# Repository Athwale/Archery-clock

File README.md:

# REV1 boards have not been built and tested yet.
If you intend to build it, please wait.

# Archery-clock
This repository contains electronic designs and software for a custom built sport archery clock used by www.patriotbrno.cz

## V2
V2 is the current design which uses a Raspberry pi 3 and is controlled over wi-fi using a smartphone or a computer.  
It is built to be more modular and easier to build or repair.

## PCBs
The DXF and Gerber files are exported from copper side and must be mirror flipped by the manufacturer to produce correct boards, KiCad does not have this functionality built in. Drill files are included, but should be checked and adjusted according to your needs.  
Check the position of pin 1 on the microcontroller (square pad in the design) for correct stencil placement.

## Control software  
The clock has a web based user interface that you can use from a wif-fi capable phone or computer.  
This software is being developed here:  
https://github.com/zmej/arclock

### Viewing the designs
Electronic designs were made in KiCad.

### Disclaimer
These designs were not professionally produced nor rigorously tested by any institution. You are building this device on your own and you accept all responsibility for it's function and operation.

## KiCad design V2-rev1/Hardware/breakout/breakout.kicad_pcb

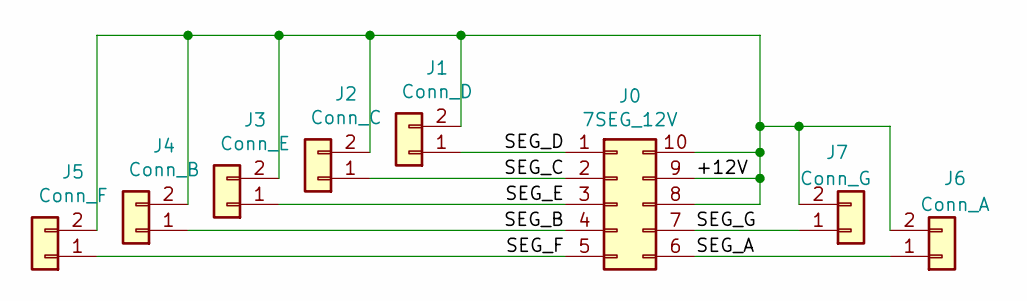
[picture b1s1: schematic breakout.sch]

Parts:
J0: 7SEG_12V; IDC-Header_2x05-1MP_P2.54mm_Latch_Vertical
J1: Conn_D; Molex_KK-254_AE-6410-02A_1x02_P2.54mm_Vertical
J2: Conn_C; Molex_KK-254_AE-6410-02A_1x02_P2.54mm_Vertical
J3: Conn_E; Molex_KK-254_AE-6410-02A_1x02_P2.54mm_Vertical
J4: Conn_B; Molex_KK-254_AE-6410-02A_1x02_P2.54mm_Vertical
J5: Conn_F; Molex_KK-254_AE-6410-02A_1x02_P2.54mm_Vertical
J6: Conn_A; Molex_KK-254_AE-6410-02A_1x02_P2.54mm_Vertical
J7: Conn_G; Molex_KK-254_AE-6410-02A_1x02_P2.54mm_Vertical

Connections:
/+12V: J0.8, J0.9, J0.10, J1.2, J2.2, J3.2, J4.2, J5.2, J6.2, J7.2
/SEG_A: J0.6, J6.1
/SEG_B: J0.4, J4.1
/SEG_C: J0.2, J2.1
/SEG_D: J0.1, J1.1
/SEG_E: J0.3, J3.1
/SEG_F: J0.5, J5.1
/SEG_G: J0.7, J7.1

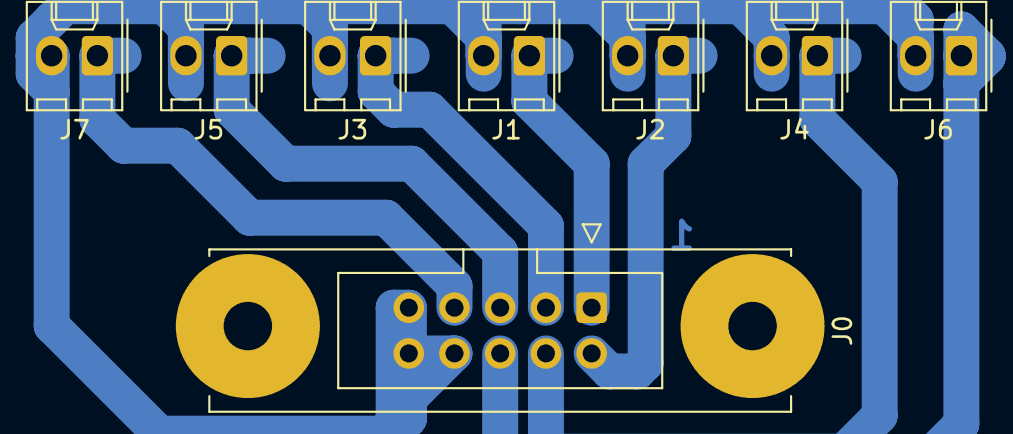
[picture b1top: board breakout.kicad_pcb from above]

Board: 2 copper layers, 12 parts (0 on the bottom side), 8 nets.

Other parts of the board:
Screw: MountingHole_3.2mm_M3
Screw#2, Screw#3, Screw#4: MountingHole_3.2mm_M3

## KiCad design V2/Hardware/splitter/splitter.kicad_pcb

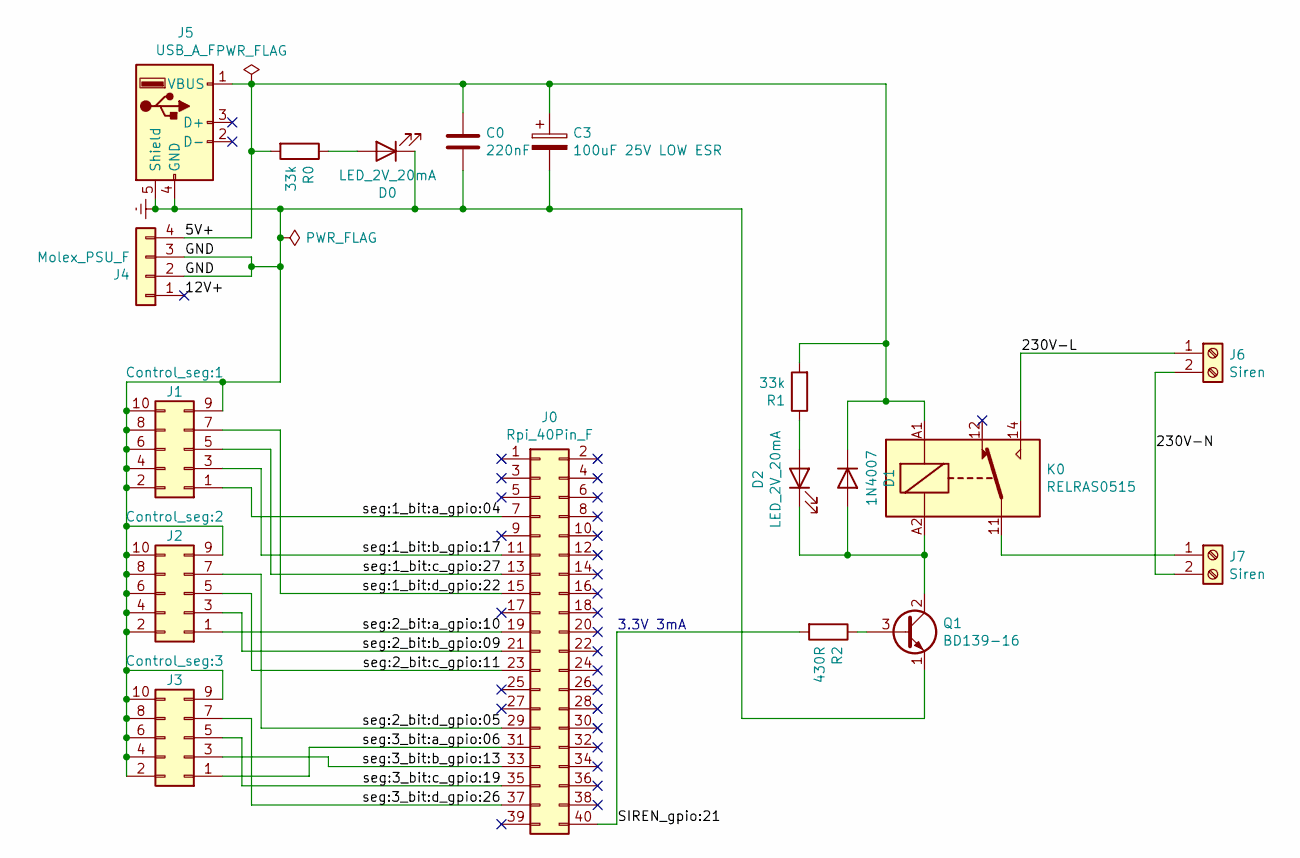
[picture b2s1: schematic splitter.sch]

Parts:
C0: 220nF; C_Disc_D4.3mm_W1.9mm_P5.00mm
C3: 100uF 25V LOW ESR; CP_Radial_D10.0mm_P5.00mm
D0, D2: LED_2V_20mA; LED_D5.0mm
D1: 1N4007; D_A-405_P10.16mm_Horizontal
J0: Rpi_40Pin_F; PinSocket_2x20_P2.54mm_Vertical
J1: Control_seg:1; IDC-Header_2x05-1MP_P2.54mm_Latch_Vertical
J2: Control_seg:2; IDC-Header_2x05-1MP_P2.54mm_Latch_Vertical
J3: Control_seg:3; IDC-Header_2x05-1MP_P2.54mm_Latch_Vertical
J4: Molex_PSU_F; conn_hdd_15-24-4449
J5: USB_A_F; USB_A_Stewart_SS-52100-001_Horizontal
J6, J7: Siren; TerminalBlock_RND_205-00067_1x02_P7.50mm_Horizontal
K0: RELRAS0515; Relay_SPDT_Finder_36.11
Q1: BD139-16; TO-126-3_Vertical
R0, R1: 33k; R_Axial_DIN0207_L6.3mm_D2.5mm_P10.16mm_Horizontal
R2: 430R; R_Axial_DIN0207_L6.3mm_D2.5mm_P10.16mm_Horizontal

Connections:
/5V+: C0.1, C3.1, D1.1 (K), J4.4, J5.1 (VBUS), K0.A1, R0.2, R1.2
/12V+: J4.1
/230V-L: J6.1, K0.14
/230V-N: J6.2, J7.2
/SIREN_gpio:21: J0.40, R2.2
/seg:1_bit:a_gpio:04: J0.7, J1.1
/seg:1_bit:b_gpio:17: J0.11, J1.3
/seg:1_bit:c_gpio:27: J0.13, J1.5
/seg:1_bit:d_gpio:22: J0.15, J1.7
/seg:2_bit:a_gpio:10: J0.19, J2.1
/seg:2_bit:b_gpio:09: J0.21, J2.3
/seg:2_bit:c_gpio:11: J0.23, J2.5
/seg:2_bit:d_gpio:05: J0.29, J2.7
/seg:3_bit:a_gpio:06: J0.31, J3.1
/seg:3_bit:b_gpio:13: J0.33, J3.3
/seg:3_bit:c_gpio:19: J0.35, J3.5
/seg:3_bit:d_gpio:26: J0.37, J3.7
Earth: C0.2, C3.2, D0.1 (K), J1.2, J1.4, J1.6, J1.8, J1.9, J1.10, J2.2, J2.4, J2.6, J2.8, J2.9, J2.10, J3.2, J3.4, J3.6, J3.8, J3.9, J3.10, J4.2, J4.3, J5.4 (GND), J5.5 (Shield), Q1.1 (E)
unnamed: D0.2 (A), R0.1
unnamed: D1.2 (A), D2.1 (K), K0.A2, Q1.2 (C)
unnamed: D2.2 (A), R1.1
unnamed: J7.1, K0.11
unnamed: Q1.3 (B), R2.1

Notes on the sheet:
3.3V 3mA

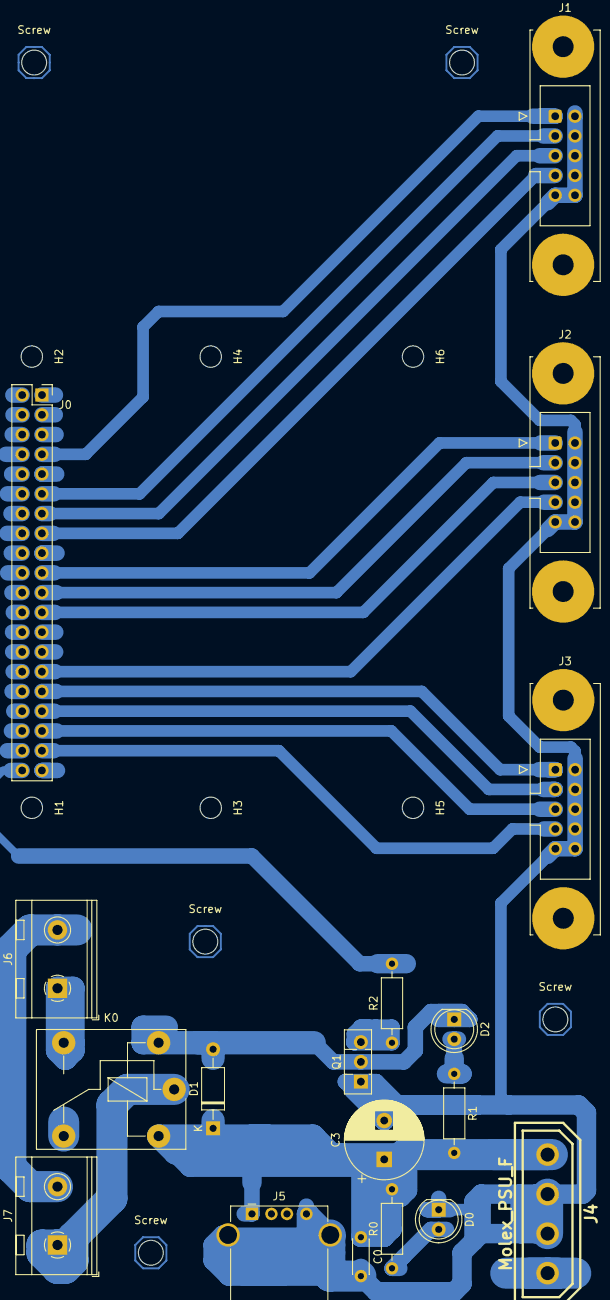
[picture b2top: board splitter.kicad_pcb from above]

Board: 2 copper layers, 29 parts (0 on the bottom side), 22 nets.

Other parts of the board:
H1, H2, H3, H4, H5, H6: MountingHole; MountingHole_2.75mm_NoPad
Screw: MountingHole_3.2mm_M3
Screw#2, Screw#3, Screw#4, Screw#5: MountingHole_3.2mm_M3

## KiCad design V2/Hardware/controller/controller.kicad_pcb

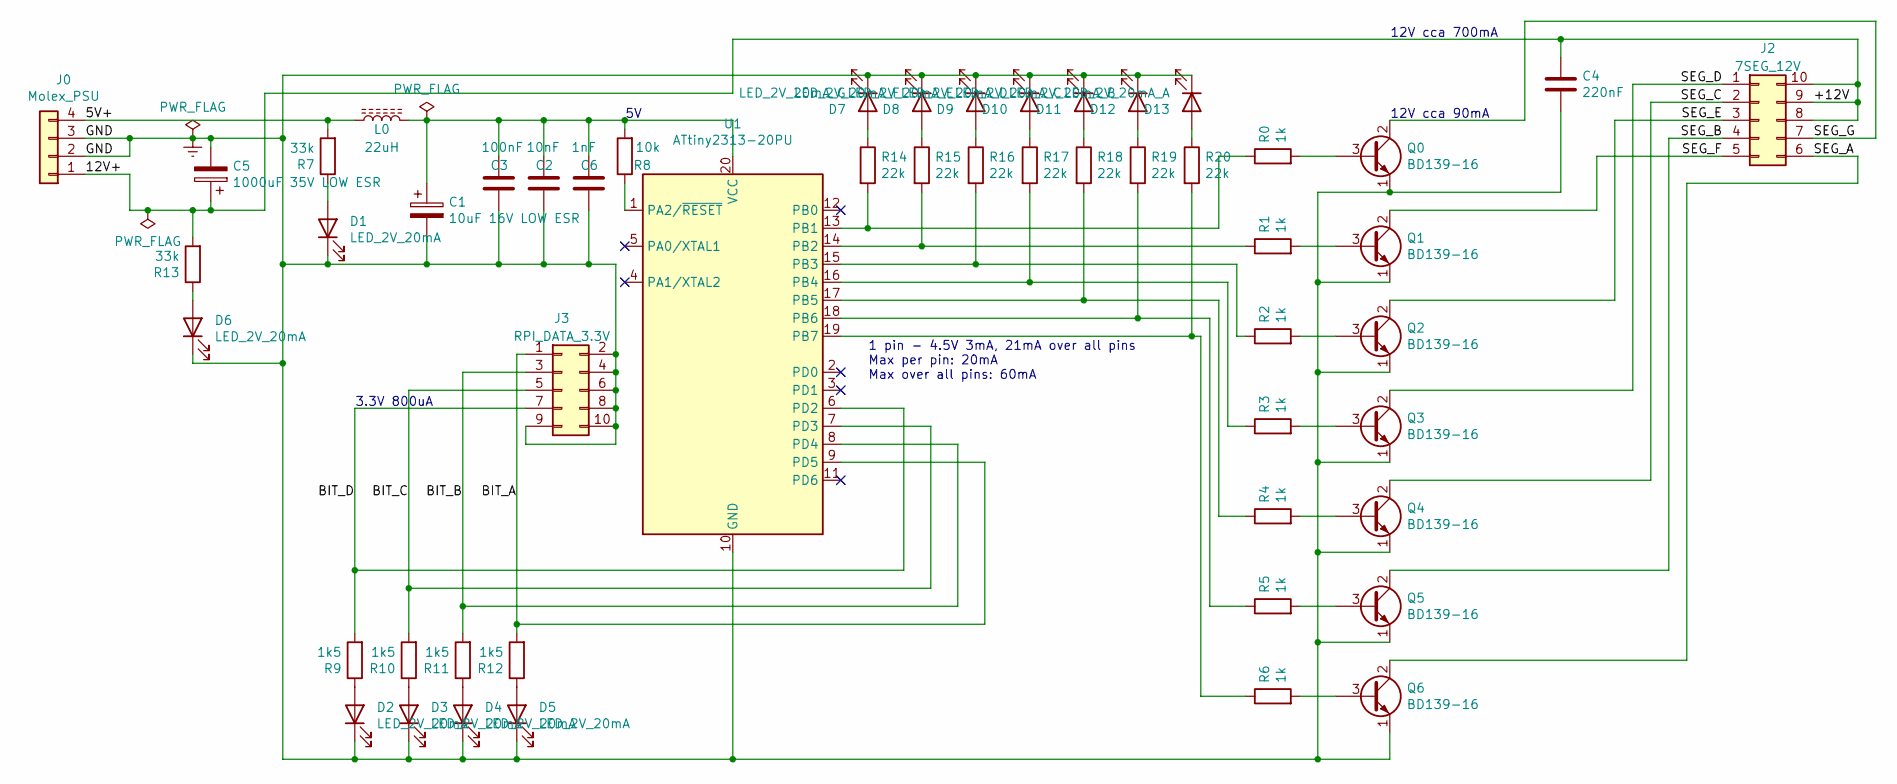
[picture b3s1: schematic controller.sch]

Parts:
C1: 10uF 16V LOW ESR; CP_Radial_D5.0mm_P2.00mm
C2: 10nF; C_Disc_D5.0mm_W2.5mm_P5.00mm
C3: 100nF; C_Disc_D5.0mm_W2.5mm_P5.00mm
C4: 220nF; C_Disc_D5.0mm_W2.5mm_P5.00mm
C5: 1000uF 35V LOW ESR; CP_Radial_D12.5mm_P5.00mm
C6: 1nF; C_Disc_D5.0mm_W2.5mm_P5.00mm
D1, D2, D3, D4, D5, D6: LED_2V_20mA; LED_D5.0mm
D7: LED_2V_20mA_G; LED_D5.0mm
D8: LED_2V_20mA_F; LED_D5.0mm
D9: LED_2V_20mA_E; LED_D5.0mm
D10: LED_2V_20mA_D; LED_D5.0mm
D11: LED_2V_20mA_C; LED_D5.0mm
D12: LED_2V_20mA_B; LED_D5.0mm
D13: LED_2V_20mA_A; LED_D5.0mm
J0: Molex_PSU; conn_hdd_15-24-4449
J2: 7SEG_12V; IDC-Header_2x05-1MP_P2.54mm_Latch_Vertical
J3: RPI_DATA_3.3V; IDC-Header_2x05-1MP_P2.54mm_Latch_Vertical
L0: 22uH; L_Axial_L7.0mm_D3.3mm_P10.16mm_Horizontal_Fastron_MICC
Q0, Q1, Q2, Q3, Q4, Q5, Q6: BD139-16; TO-126-3_Vertical
R0, R1, R2, R3, R4, R5, R6: 1k; R_Axial_DIN0207_L6.3mm_D2.5mm_P10.16mm_Horizontal
R7, R13: 33k; R_Axial_DIN0207_L6.3mm_D2.5mm_P10.16mm_Horizontal
R8: 10k; R_Axial_DIN0207_L6.3mm_D2.5mm_P10.16mm_Horizontal
R9, R10, R11, R12: 1k5; R_Axial_DIN0207_L6.3mm_D2.5mm_P10.16mm_Horizontal
R14, R18, R19, R20: 22k; R_Axial_DIN0207_L6.3mm_D2.5mm_P10.16mm_Horizontal
R15, R16, R17: 22k; R_Axial_DIN0207_L6.3mm_D2.5mm_P15.24mm_Horizontal
U1: ATtiny2313-20PU; DIP-20_W7.62mm

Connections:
/5V+: J0.4, L0.1, R7.2
/+12V: C4.1, C5.1, J0.1, J2.8, J2.9, J2.10, R13.2
/BIT_A: J3.1, R12.2, U1.9 (PD5)
/BIT_B: J3.3, R11.2, U1.8 (PD4)
/BIT_C: J3.5, R10.2, U1.7 (PD3)
/BIT_D: J3.7, R9.2, U1.6 (PD2)
/SEG_A: J2.6, Q6.2 (C)
/SEG_B: J2.4, Q5.2 (C)
/SEG_C: J2.2, Q4.2 (C)
/SEG_D: J2.1, Q3.2 (C)
/SEG_E: J2.3, Q2.2 (C)
/SEG_F: J2.5, Q1.2 (C)
/SEG_G: J2.7, Q0.2 (C)
Earth: C1.2, C2.2, C3.2, C4.2, C5.2, C6.2, D1.1 (K), D2.1 (K), D3.1 (K), D4.1 (K), D5.1 (K), D6.1 (K), D7.1 (K), D8.1 (K), D9.1 (K), D10.1 (K), D11.1 (K), D12.1 (K), D13.1 (K), J0.2, J0.3, J3.2, J3.4, J3.6, J3.8, J3.9, J3.10, Q0.1 (E), Q1.1 (E), Q2.1 (E), Q3.1 (E), Q4.1 (E), Q5.1 (E), Q6.1 (E), U1.10 (GND)
unnamed: C1.1, C2.1, C3.1, C6.1, L0.2, R8.2, U1.20 (VCC)
unnamed: D1.2 (A), R7.1
unnamed: D2.2 (A), R9.1
unnamed: D3.2 (A), R10.1
unnamed: D4.2 (A), R11.1
unnamed: D5.2 (A), R12.1
unnamed: D6.2 (A), R13.1
unnamed: D7.2 (A), R14.1
unnamed: D8.2 (A), R15.1
unnamed: D9.2 (A), R16.1
unnamed: D10.2 (A), R17.1
unnamed: D11.2 (A), R18.1
unnamed: D12.2 (A), R19.1
unnamed: D13.2 (A), R20.1
unnamed: Q0.3 (B), R0.2
unnamed: Q1.3 (B), R1.2
unnamed: Q2.3 (B), R2.2
unnamed: Q3.3 (B), R3.2
unnamed: Q4.3 (B), R4.2
unnamed: Q5.3 (B), R5.2
unnamed: Q6.3 (B), R6.2
unnamed: R0.1, R14.2, U1.13 (PB1)
unnamed: R1.1, R15.2, U1.14 (PB2)
unnamed: R8.1, U1.1 (PA2/~RESET)
unnamed: R2.1, R16.2, U1.15 (PB3)
unnamed: R3.1, R17.2, U1.16 (PB4)
unnamed: R4.1, R18.2, U1.17 (PB5)
unnamed: R5.1, R19.2, U1.18 (PB6)
unnamed: R6.1, R20.2, U1.19 (PB7)

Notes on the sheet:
12V cca 90mA
12V cca 700mA
1 pin - 4.5V 3mA, 21mA over all pins Max per pin: 20mA Max over all pins: 60mA
3.3V 800uA

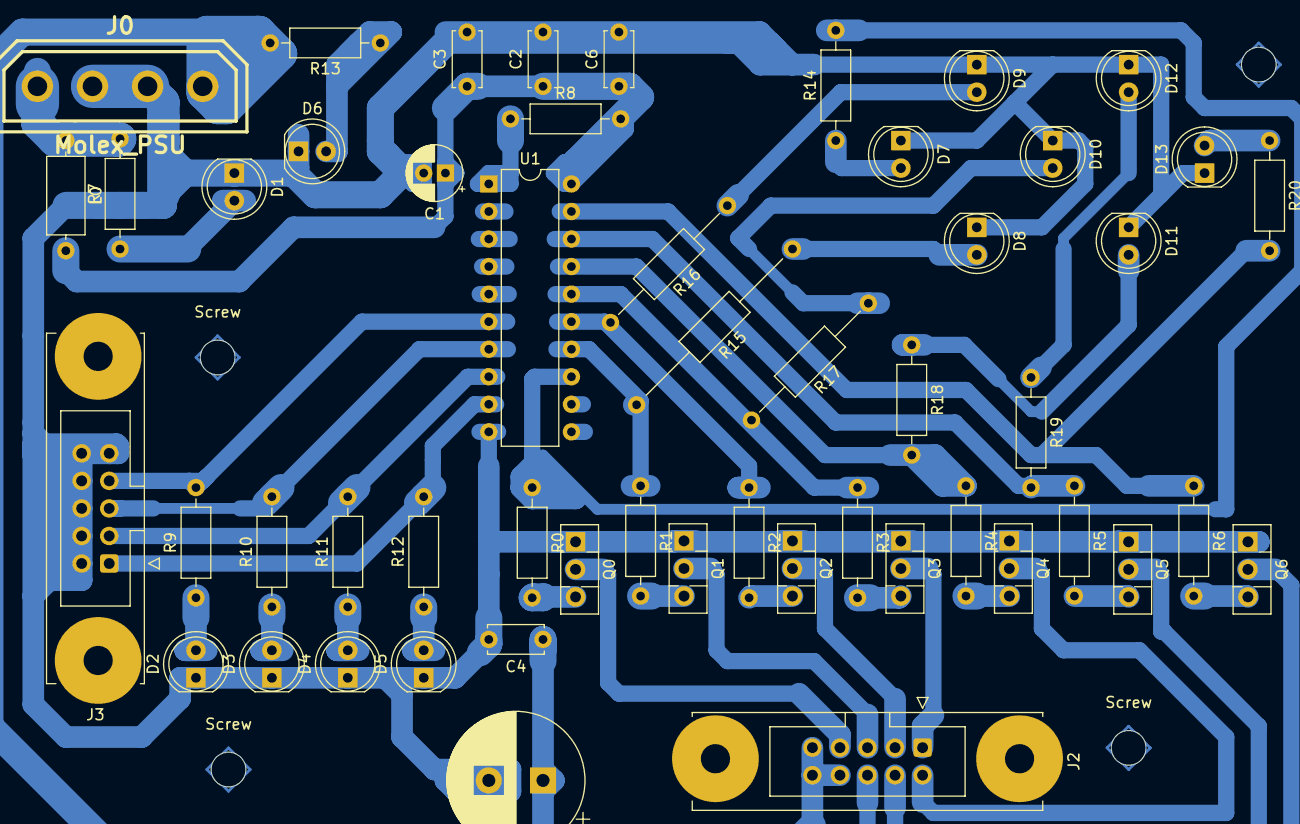
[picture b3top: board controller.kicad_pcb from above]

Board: 2 copper layers, 56 parts (0 on the bottom side), 43 nets.

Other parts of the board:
Screw: MountingHole_3.2mm_M3
Screw#2, Screw#3, Screw#4: MountingHole_3.2mm_M3

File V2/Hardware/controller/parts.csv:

"Id";"Designator";"Package";"Quantity";"Designation";"Supplier and ref";
1;"C5";"CP_Radial_D13.0mm_P5.00mm";1;"1000uF 35V LOW ESR";;;
2;"C4";"C_Disc_D5.0mm_W2.5mm_P5.00mm";1;"220nF";;;
3;"C3";"C_Disc_D5.0mm_W2.5mm_P5.00mm";1;"100nF";;;
4;"C1";"CP_Radial_D10.0mm_P5.00mm";1;"47uF";;;
5;"C2";"C_Disc_D5.0mm_W2.5mm_P5.00mm";1;"10nF";;;
6;"J2";"PinHeader_2x05_P2.54mm_Horizontal";1;"Flat_7seg_F";;;
7;"R14,R18,R19,R20";"R_Axial_DIN0207_L6.3mm_D2.5mm_P10.16mm_Horizontal";4;"22k";;;
8;"R15,R16,R17";"R_Axial_DIN0207_L6.3mm_D2.5mm_P15.24mm_Horizontal";3;"22k";;;
9;"U1";"DIP-20_W7.62mm";1;"ATtiny2313-20PU";;;
10;"D1,D2,D3,D4,D5,D6";"LED_D5.0mm";6;"LED_2V_20mA";;;
11;"D7";"LED_D5.0mm";1;"LED_2V_20mA_G";;;
12;"D8";"LED_D5.0mm";1;"LED_2V_20mA_F";;;
13;"D9";"LED_D5.0mm";1;"LED_2V_20mA_E";;;
14;"D10";"LED_D5.0mm";1;"LED_2V_20mA_D";;;
15;"D11";"LED_D5.0mm";1;"LED_2V_20mA_C";;;
16;"D12";"LED_D5.0mm";1;"LED_2V_20mA_B";;;
17;"D13";"LED_D5.0mm";1;"LED_2V_20mA_A";;;
18;"J0";"conn_hdd_15-24-4441";1;"Molex_PSU_F";;;
19;"J3";"PinHeader_2x03_P2.54mm_Horizontal";1;"Rpi_DATA_F_3.3V";;;
20;"Q0,Q1,Q2,Q3,Q4,Q5,Q6";"TO-126-3_Vertical";7;"BD139-16";;;
21;"R0,R1,R2,R3,R4,R5,R6";"R_Axial_DIN0207_L6.3mm_D2.5mm_P10.16mm_Horizontal";7;"1k";;;
22;"R7,R13";"R_Axial_DIN0207_L6.3mm_D2.5mm_P10.16mm_Horizontal";2;"33k";;;
23;"R8";"R_Axial_DIN0207_L6.3mm_D2.5mm_P10.16mm_Horizontal";1;"10k";;;
24;"R9,R10,R11,R12";"R_Axial_DIN0207_L6.3mm_D2.5mm_P10.16mm_Horizontal";4;"1k5";;;

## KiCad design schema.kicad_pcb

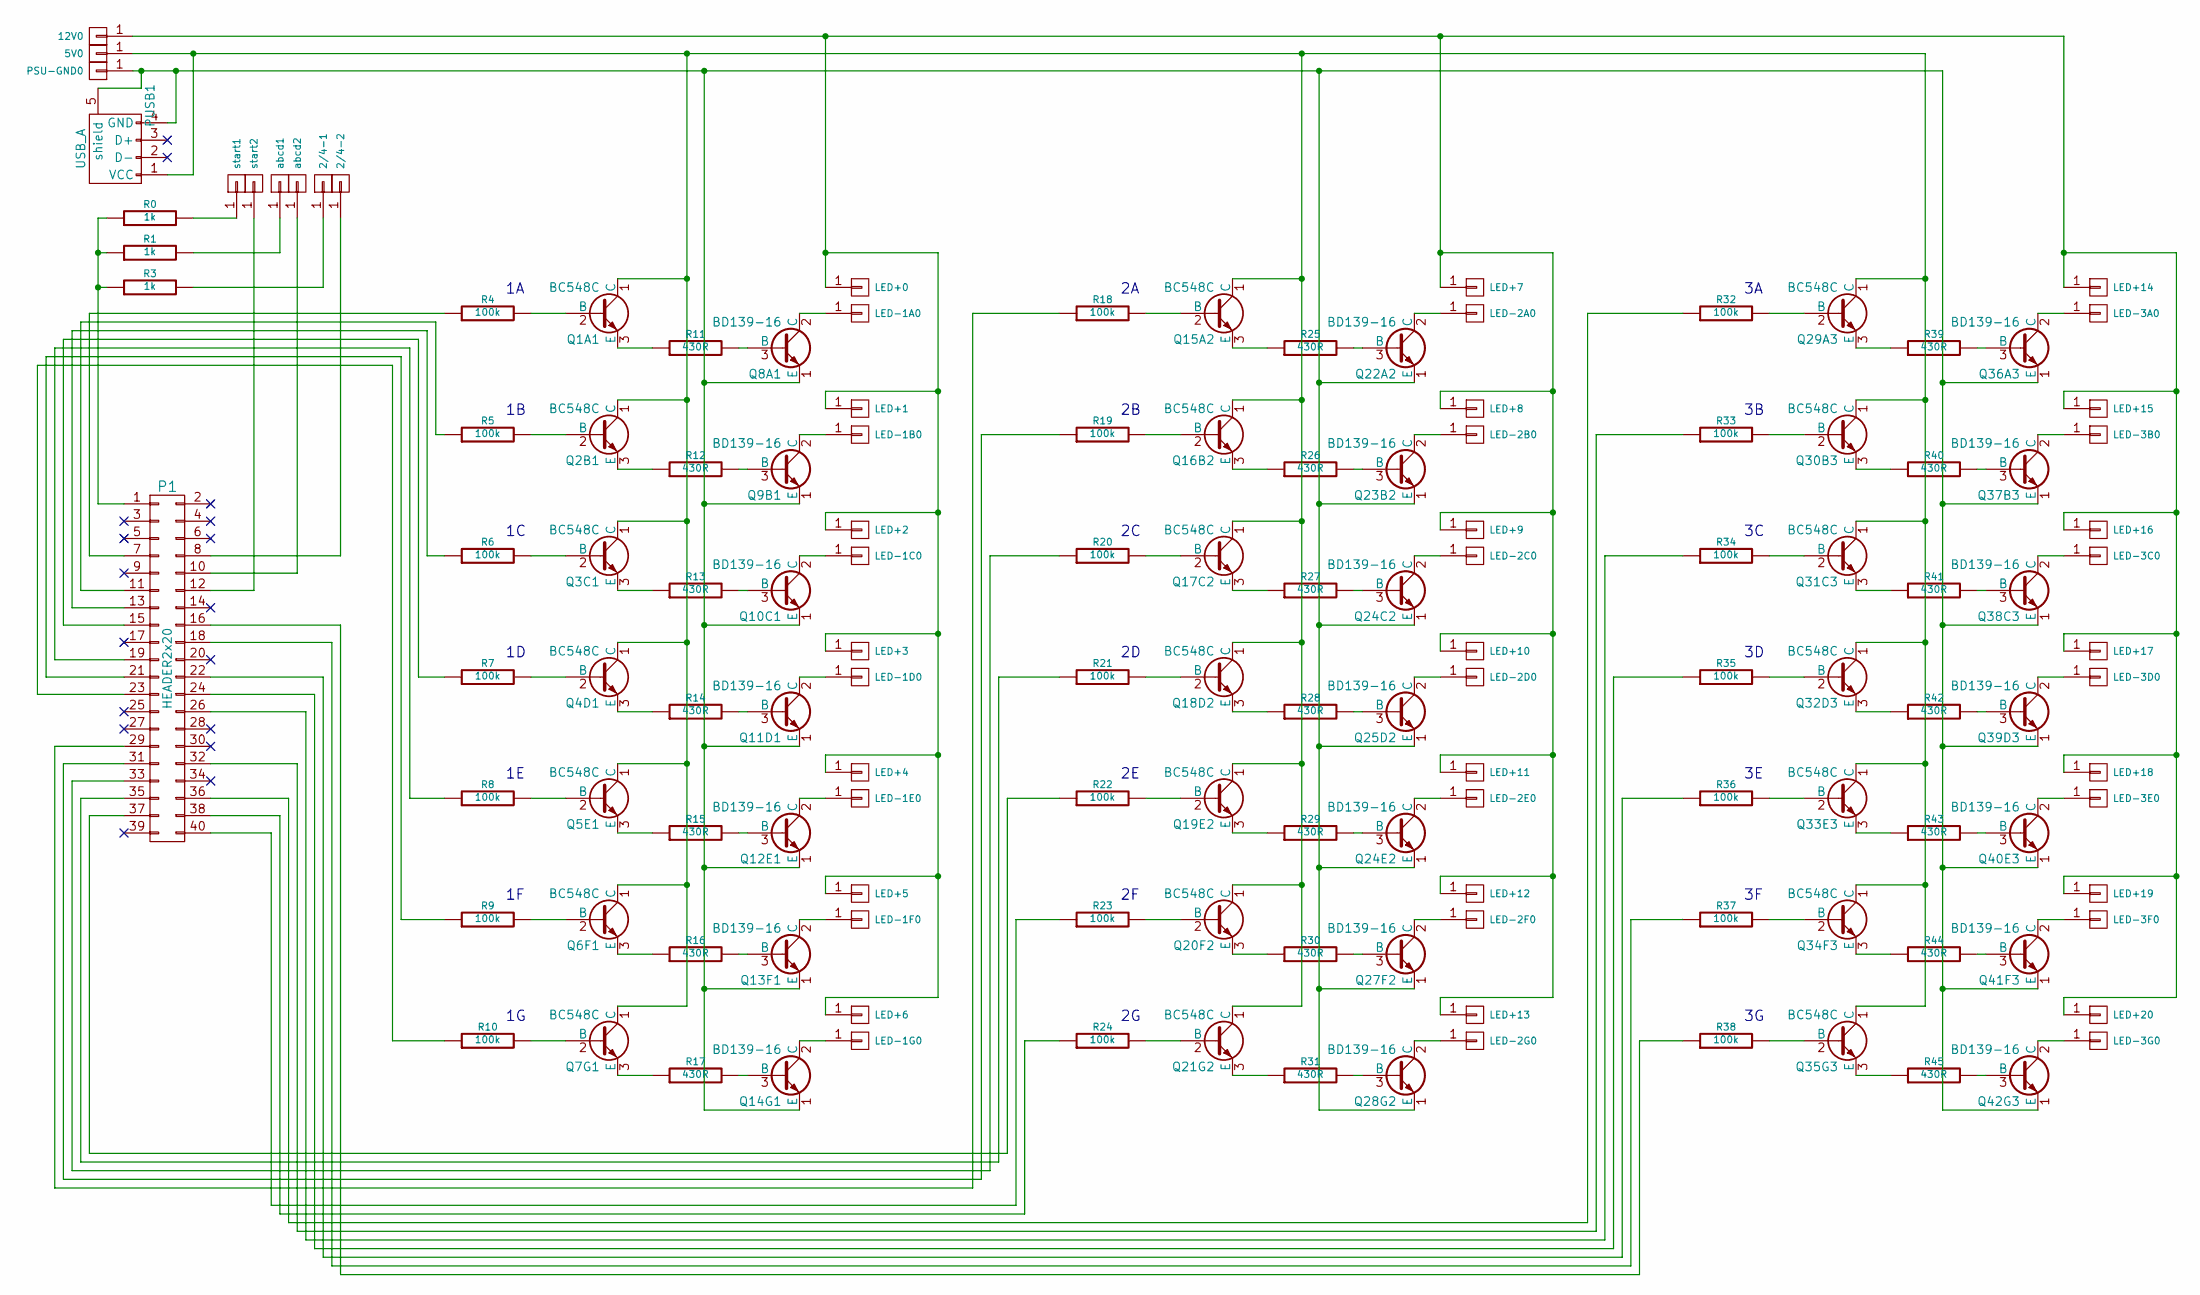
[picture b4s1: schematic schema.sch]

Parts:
2/4-1: 2/4-1; SolderWirePad_single_0-8mmDrill
2/4-2: 2/4-2; SolderWirePad_single_0-8mmDrill
5V0: 5V; SolderWirePad_single_0-8mmDrill
12V0: 12V; SolderWirePad_single_0-8mmDrill
LED+0, LED+1, LED+2, LED+3, LED+4, LED+5, LED+6, LED+7, LED+8, LED+9, LED+10, LED+11, LED+12, LED+13, LED+14, LED+15, LED+16, LED+17, LED+18, LED+19, LED+20: 12V; SolderWirePad_single_0-8mmDrill
LED-1A0, LED-1B0, LED-1C0, LED-1D0, LED-1E0, LED-1F0, LED-1G0, LED-2A0, LED-2B0, LED-2C0, LED-2D0, LED-2E0, LED-2F0, LED-2G0, LED-3A0, LED-3B0, LED-3C0, LED-3D0, LED-3E0, LED-3F0, LED-3G0: 12V; SolderWirePad_single_0-8mmDrill
P1: HEADER2x20; IDC_Header_Straight_40pins
PSU-GND0: 12V GND; SolderWirePad_single_0-8mmDrill
PUSB1: USB_A
Q1A1, Q2B1, Q3C1, Q4D1, Q5E1, Q6F1, Q7G1, Q15A2, Q16B2, Q17C2, Q18D2, Q19E2, Q20F2, Q21G2, Q29A3, Q30B3, Q31C3, Q32D3, Q33E3, Q34F3, Q35G3: BC548C; TO-92_Inline_Wide
Q8A1, Q9B1, Q10C1, Q11D1, Q12E1, Q13F1, Q14G1, Q22A2, Q23B2, Q24C2, Q24E2, Q25D2, Q27F2, Q28G2, Q36A3, Q37B3, Q38C3, Q39D3, Q40E3, Q41F3, Q42G3: BD139-16; SOT126_SOT32_Housing_Vertical
R0, R1, R3: 1k; Resistor_Horizontal_RM10mm
R4, R5, R6, R7, R8, R9, R10, R18, R19, R20, R21, R22, R23, R24, R32, R33, R34, R35, R36, R37, R38: 100k; Resistor_Horizontal_RM10mm
R11, R12, R13, R14, R15, R16, R17, R25, R26, R27, R28, R29, R30, R31, R39, R40, R41, R42, R43, R44, R45: 430R; Resistor_Horizontal_RM15mm
abcd1: abcd1; SolderWirePad_single_0-8mmDrill
abcd2: abcd2; SolderWirePad_single_0-8mmDrill
start1: start1; SolderWirePad_single_0-8mmDrill
start2: start2; SolderWirePad_single_0-8mmDrill

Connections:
unnamed: 2/4-1.1, R3.2
unnamed: 2/4-2.1, P1.8
unnamed: 5V0.1, PUSB1.1 (VCC), Q1A1.1 (C), Q2B1.1 (C), Q3C1.1 (C), Q4D1.1 (C), Q5E1.1 (C), Q6F1.1 (C), Q7G1.1 (C), Q15A2.1 (C), Q16B2.1 (C), Q17C2.1 (C), Q18D2.1 (C), Q19E2.1 (C), Q20F2.1 (C), Q21G2.1 (C), Q29A3.1 (C), Q30B3.1 (C), Q31C3.1 (C), Q32D3.1 (C), Q33E3.1 (C), Q34F3.1 (C), Q35G3.1 (C)
unnamed 3: 12V0.1, LED+0.1, LED+1.1, LED+2.1, LED+3.1, LED+4.1, LED+5.1, LED+6.1, LED+7.1, LED+8.1, LED+9.1, LED+10.1, LED+11.1, LED+12.1, LED+13.1, LED+14.1, LED+15.1, LED+16.1, LED+17.1, LED+18.1, LED+19.1, LED+20.1; also elsewhere on the board
unnamed: LED-1A0.1, Q8A1.2 (C)
unnamed: LED-1B0.1, Q9B1.2 (C)
unnamed: LED-1C0.1, Q10C1.2 (C)
unnamed: LED-1D0.1, Q11D1.2 (C)
unnamed: LED-1E0.1, Q12E1.2 (C)
unnamed: LED-1F0.1, Q13F1.2 (C)
unnamed: LED-1G0.1, Q14G1.2 (C)
unnamed: LED-2A0.1, Q22A2.2 (C)
unnamed: LED-2B0.1, Q23B2.2 (C)
unnamed: LED-2C0.1, Q24C2.2 (C)
unnamed: LED-2D0.1, Q25D2.2 (C)
unnamed: LED-2E0.1, Q24E2.2 (C)
unnamed: LED-2F0.1, Q27F2.2 (C)
unnamed: LED-2G0.1, Q28G2.2 (C)
unnamed: LED-3A0.1, Q36A3.2 (C)
unnamed: LED-3B0.1, Q37B3.2 (C)
unnamed: LED-3C0.1, Q38C3.2 (C)
unnamed: LED-3D0.1, Q39D3.2 (C)
unnamed: LED-3E0.1, Q40E3.2 (C)
unnamed: LED-3F0.1, Q41F3.2 (C)
unnamed: LED-3G0.1, Q42G3.2 (C)
unnamed: P1.1, R0.1, R1.1, R3.1
unnamed: P1.7, R4.1
unnamed: P1.10, abcd2.1
unnamed: P1.11, R5.1
unnamed: P1.12, start2.1
unnamed: P1.13, R6.1
unnamed: P1.15, R7.1
unnamed: P1.16, R38.1
unnamed: P1.18, R37.1
unnamed: P1.19, R8.1
unnamed: P1.21, R9.1
unnamed: P1.22, R36.1
unnamed: P1.23, R10.1
unnamed: P1.24, R35.1
unnamed: P1.26, R34.1
unnamed: P1.29, R18.1
unnamed: P1.31, R19.1
unnamed: P1.32, R33.1
unnamed: P1.33, R20.1
unnamed: P1.35, R21.1
unnamed: P1.36, R32.1
unnamed: P1.37, R22.1
unnamed: P1.38, R24.1
unnamed: P1.40, R23.1
unnamed: PSU-GND0.1, PUSB1.4 (GND), PUSB1.5 (shield), Q8A1.1 (E), Q9B1.1 (E), Q10C1.1 (E), Q11D1.1 (E), Q12E1.1 (E), Q13F1.1 (E), Q14G1.1 (E), Q22A2.1 (E), Q23B2.1 (E), Q24C2.1 (E), Q24E2.1 (E), Q25D2.1 (E), Q27F2.1 (E), Q28G2.1 (E), Q36A3.1 (E), Q37B3.1 (E), Q38C3.1 (E), Q39D3.1 (E), Q40E3.1 (E), Q41F3.1 (E), Q42G3.1 (E)
unnamed: Q1A1.2 (B), R4.2
unnamed: Q1A1.3 (E), R11.1
unnamed: Q2B1.2 (B), R5.2
unnamed: Q2B1.3 (E), R12.1
unnamed: Q3C1.2 (B), R6.2
unnamed: Q3C1.3 (E), R13.1
unnamed: Q4D1.2 (B), R7.2
unnamed: Q4D1.3 (E), R14.1
unnamed: Q5E1.2 (B), R8.2
unnamed: Q5E1.3 (E), R15.1
unnamed: Q6F1.2 (B), R9.2
unnamed: Q6F1.3 (E), R16.1
unnamed: Q7G1.2 (B), R10.2
unnamed: Q7G1.3 (E), R17.1
unnamed: Q8A1.3 (B), R11.2
unnamed: Q9B1.3 (B), R12.2
unnamed: Q10C1.3 (B), R13.2
unnamed: Q11D1.3 (B), R14.2
unnamed: Q12E1.3 (B), R15.2
unnamed: Q13F1.3 (B), R16.2
unnamed: Q14G1.3 (B), R17.2
unnamed: Q15A2.2 (B), R18.2
unnamed: Q15A2.3 (E), R25.1
unnamed: Q16B2.2 (B), R19.2
unnamed: Q16B2.3 (E), R26.1
unnamed: Q17C2.2 (B), R20.2
unnamed: Q17C2.3 (E), R27.1
unnamed: Q18D2.2 (B), R21.2
unnamed: Q18D2.3 (E), R28.1
unnamed: Q19E2.2 (B), R22.2
unnamed: Q19E2.3 (E), R29.1
unnamed: Q20F2.2 (B), R23.2
unnamed: Q20F2.3 (E), R30.1
unnamed: Q21G2.2 (B), R24.2
unnamed: Q21G2.3 (E), R31.1
unnamed: Q22A2.3 (B), R25.2
unnamed: Q23B2.3 (B), R26.2
unnamed: Q24C2.3 (B), R27.2
unnamed: Q24E2.3 (B), R29.2
unnamed: Q25D2.3 (B), R28.2
unnamed: Q27F2.3 (B), R30.2
unnamed: Q28G2.3 (B), R31.2
unnamed: Q29A3.2 (B), R32.2
unnamed: Q29A3.3 (E), R39.1
unnamed: Q30B3.2 (B), R33.2
unnamed: Q30B3.3 (E), R40.1
unnamed: Q31C3.2 (B), R34.2
unnamed: Q31C3.3 (E), R41.1
unnamed: Q32D3.2 (B), R35.2
unnamed: Q32D3.3 (E), R42.1
unnamed: Q33E3.2 (B), R36.2
unnamed: Q33E3.3 (E), R43.1
unnamed: Q34F3.2 (B), R37.2
unnamed: Q34F3.3 (E), R44.1
unnamed: Q35G3.2 (B), R38.2
unnamed: Q35G3.3 (E), R45.1
unnamed: Q36A3.3 (B), R39.2
unnamed: Q37B3.3 (B), R40.2
unnamed: Q38C3.3 (B), R41.2
unnamed: Q39D3.3 (B), R42.2
unnamed: Q40E3.3 (B), R43.2
unnamed: Q41F3.3 (B), R44.2
unnamed: Q42G3.3 (B), R45.2
unnamed: R0.2, start1.1
unnamed: R1.2, abcd1.1

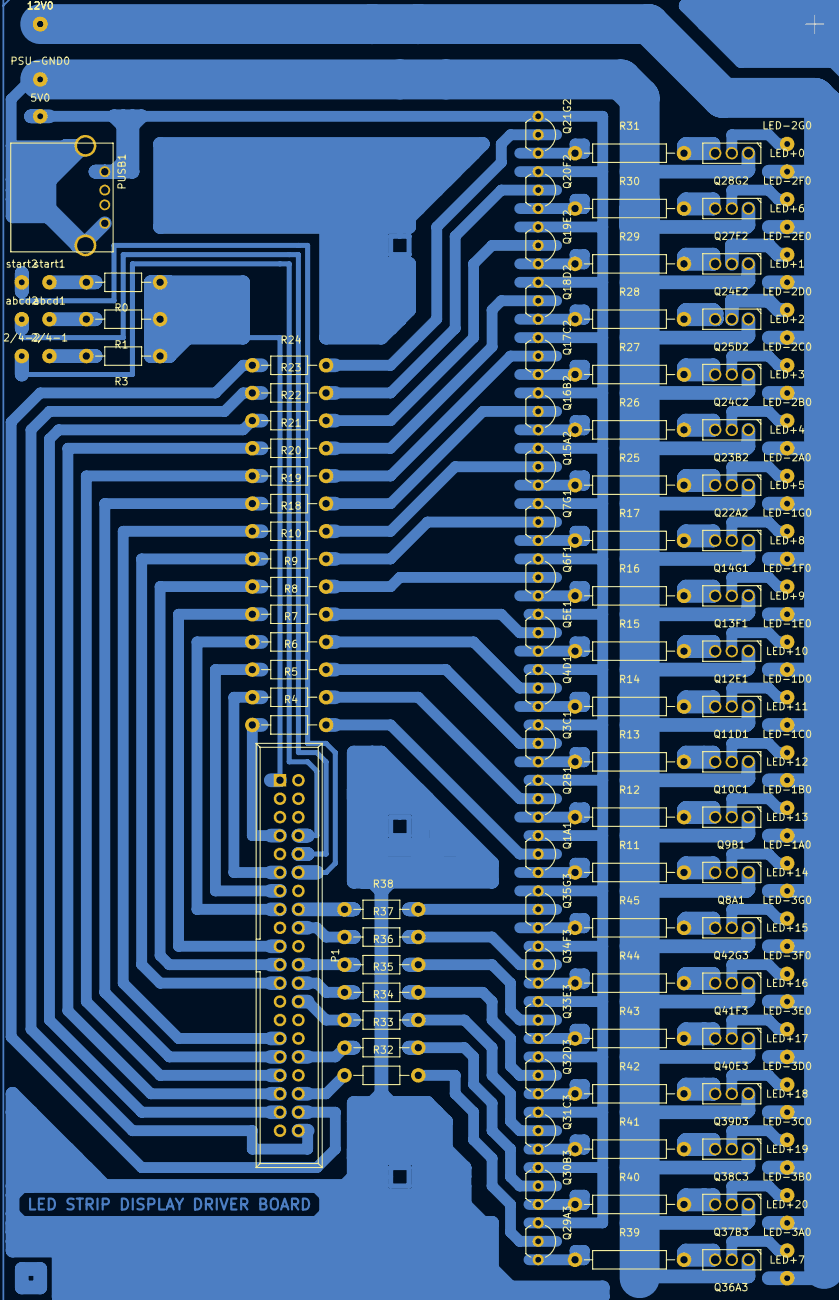
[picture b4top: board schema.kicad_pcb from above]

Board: 2 copper layers, 141 parts (0 on the bottom side), 115 nets.

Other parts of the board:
12V0#2: 12V; SolderWirePad_single_0-8mmDrill

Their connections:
unnamed 3: 12V0#2.1; also elsewhere on the board

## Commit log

2020-04-21 Adding kicad sources
2020-04-21 Create LICENSE
2020-04-22 Add controller board schematics
2020-04-22 Move files
2020-04-22 Switch driver IC
2020-04-23 Solving ERC
2020-05-02 Add gpio test
2020-05-02 Identify control pins
2020-05-03 Splitter schema
2020-05-29 finish splitter schema
2020-05-29 Add control LED
2020-05-31 Assign footprints
2020-06-05 Assign parts
2020-06-13 Add part list
2020-10-26 swicth for avr
2020-11-10 Add programmer test
2020-11-10 Add information
2020-11-10 prettify
2020-11-10 add md readmes
2020-11-11 Reading input 1:1
2020-11-12 Finish decoder and add io test
2020-11-12 Update doc
2020-11-12 doc update
2020-11-12 Update schematics
2020-11-16 update schemas
2020-11-17 update schematic
2020-11-18 Add controller board
2020-11-18 Finish PCBs
2020-11-19 Reinforce output
2020-11-20 Add display breakout board
2020-11-21 Export -pcbs
2020-11-23 Update resistor values
2020-11-23 Fix relay symbol
2020-11-23 Update design
2020-11-25 Update splitter board
2020-11-25 Make more precise plots
2020-11-25 Simplify relay control
2020-11-26 Add bypass caps and filtering
2020-11-26 More separation
2020-11-26 Add images of laouts and schemas
2020-11-26 Old version, do not use
2020-11-26 Add kicad part lists
2020-11-29 Add various exports
2021-01-15 Add dxf export
2021-02-15 Add drill files
2021-02-18 Update files
2021-02-19 Regenerate pdfs
2021-02-21 Redefine A and C
2021-02-28 fix number 6
2021-03-01 code fix
2021-03-03 Remove parts - confusing
2021-03-03 update capacitors
2021-03-03 Development notice
2021-03-18 test add
2021-03-18 Remove wrong folder
2021-04-25 Update splitter
2021-04-25 Update controller
2021-05-08 solve input interference
2021-06-06 add guide
2021-06-10 revision 2 boards
2021-06-14 Remove version 1 board
2021-06-14 Redesign for sandwich pi
2021-06-14 clean up files
2021-06-14 Mark revisioin
2021-06-14 Add old revison 0 boards
2021-06-15 make way for usb
2021-06-26 mark pin 1
2021-06-26 reinforce some copper
2021-06-26 move pin mark
